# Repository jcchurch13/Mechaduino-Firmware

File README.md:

New release 11/26/2018!  The calibration table is now stored in flash memory!  (Many thanks to osresearch!) We've also fixed a couple of small bugs.
Here are some preliminary instructions on how to get your Mechaduino up and running.  For more details, see the Mechaduino Manual above!

## Bootloader:
You will need to make sure your Mechaduino has the latest Arduino Zero bootloader.  If you got your Mechaduino from Tropical Labs, it will already have this! Otherwise you will need an Atmel-ICE or similar SWD programmer...

## Firmware:

Compile the Mechaduino firmware in the Arduino IDE and upload to your Mechaduino.  (Mechaduino will appear as an Arduino Zero.)  

New firmware is in the default "master" branch. Older versions are available [here](https://github.com/jcchurch13/Mechaduino-Firmware/releases). 

## Calibration Routine:

The first thing you will need to do is run the encoder calibration routine.

With the Mechaduino connected to your computer, open a serial monitor (115200 baud) in the Arduino IDE.  You will need to provide V+ to the Mechaduino to power the motor drivers (needed to calibrate).  A menu should appear explaining the basic commands (you can call the menu up at any time by typing 'm').  Type "s" and press enter a couple times to verify that everything is working.  The Mechaduino should step like a stepper.  It is currently in open loop mode.  press "d" and the stepping direction will change.  

Now, make sure nothing will touch the Mechaduino’s shaft during the calibration routine. If possible, completely disconnect any load that is attached to the Mechaduino’s shaft.  Type "c" to start the calibration routine. The Mechaduino will now step through all full steps to calibrate the encoder. In the latest version of the firmware, the calibration table will automatically be stored in non-volatile flash memory. When this routine is complete, your Mechaduino is now calibrated!

## Basic Commands:

As long as you have "serialCheck();" in your main loop, you can use the following built in commands to control the mechaduino from a serial monitor:

s - step (steps one full step in open loop mode)

d - dir (changes step direction in open loop mode)

p - print angle [step count] , [assumed angle] , [encoder reading]

c - calibration routine

e - check encoder diagnostics

q - parameter query (prints current PID values and cal table)

x  -  position mode

v - velocity mode

t - torque mode

y - enable control loop (enter closed loop mode)

n - disable control loop (go back to open loop mode)

r - enter new setpoint (new setpoint for control loop)

j - step response

k - edit controller gains*

g - generate sine commutation table

m - print main menu

  ...see serialCheck() in Utils for more details

##License

All Mechaduino related materials are released under the
[Creative Commons Attribution Share-Alike 4.0 License](https://creativecommons.org/licenses/by-sa/4.0/)

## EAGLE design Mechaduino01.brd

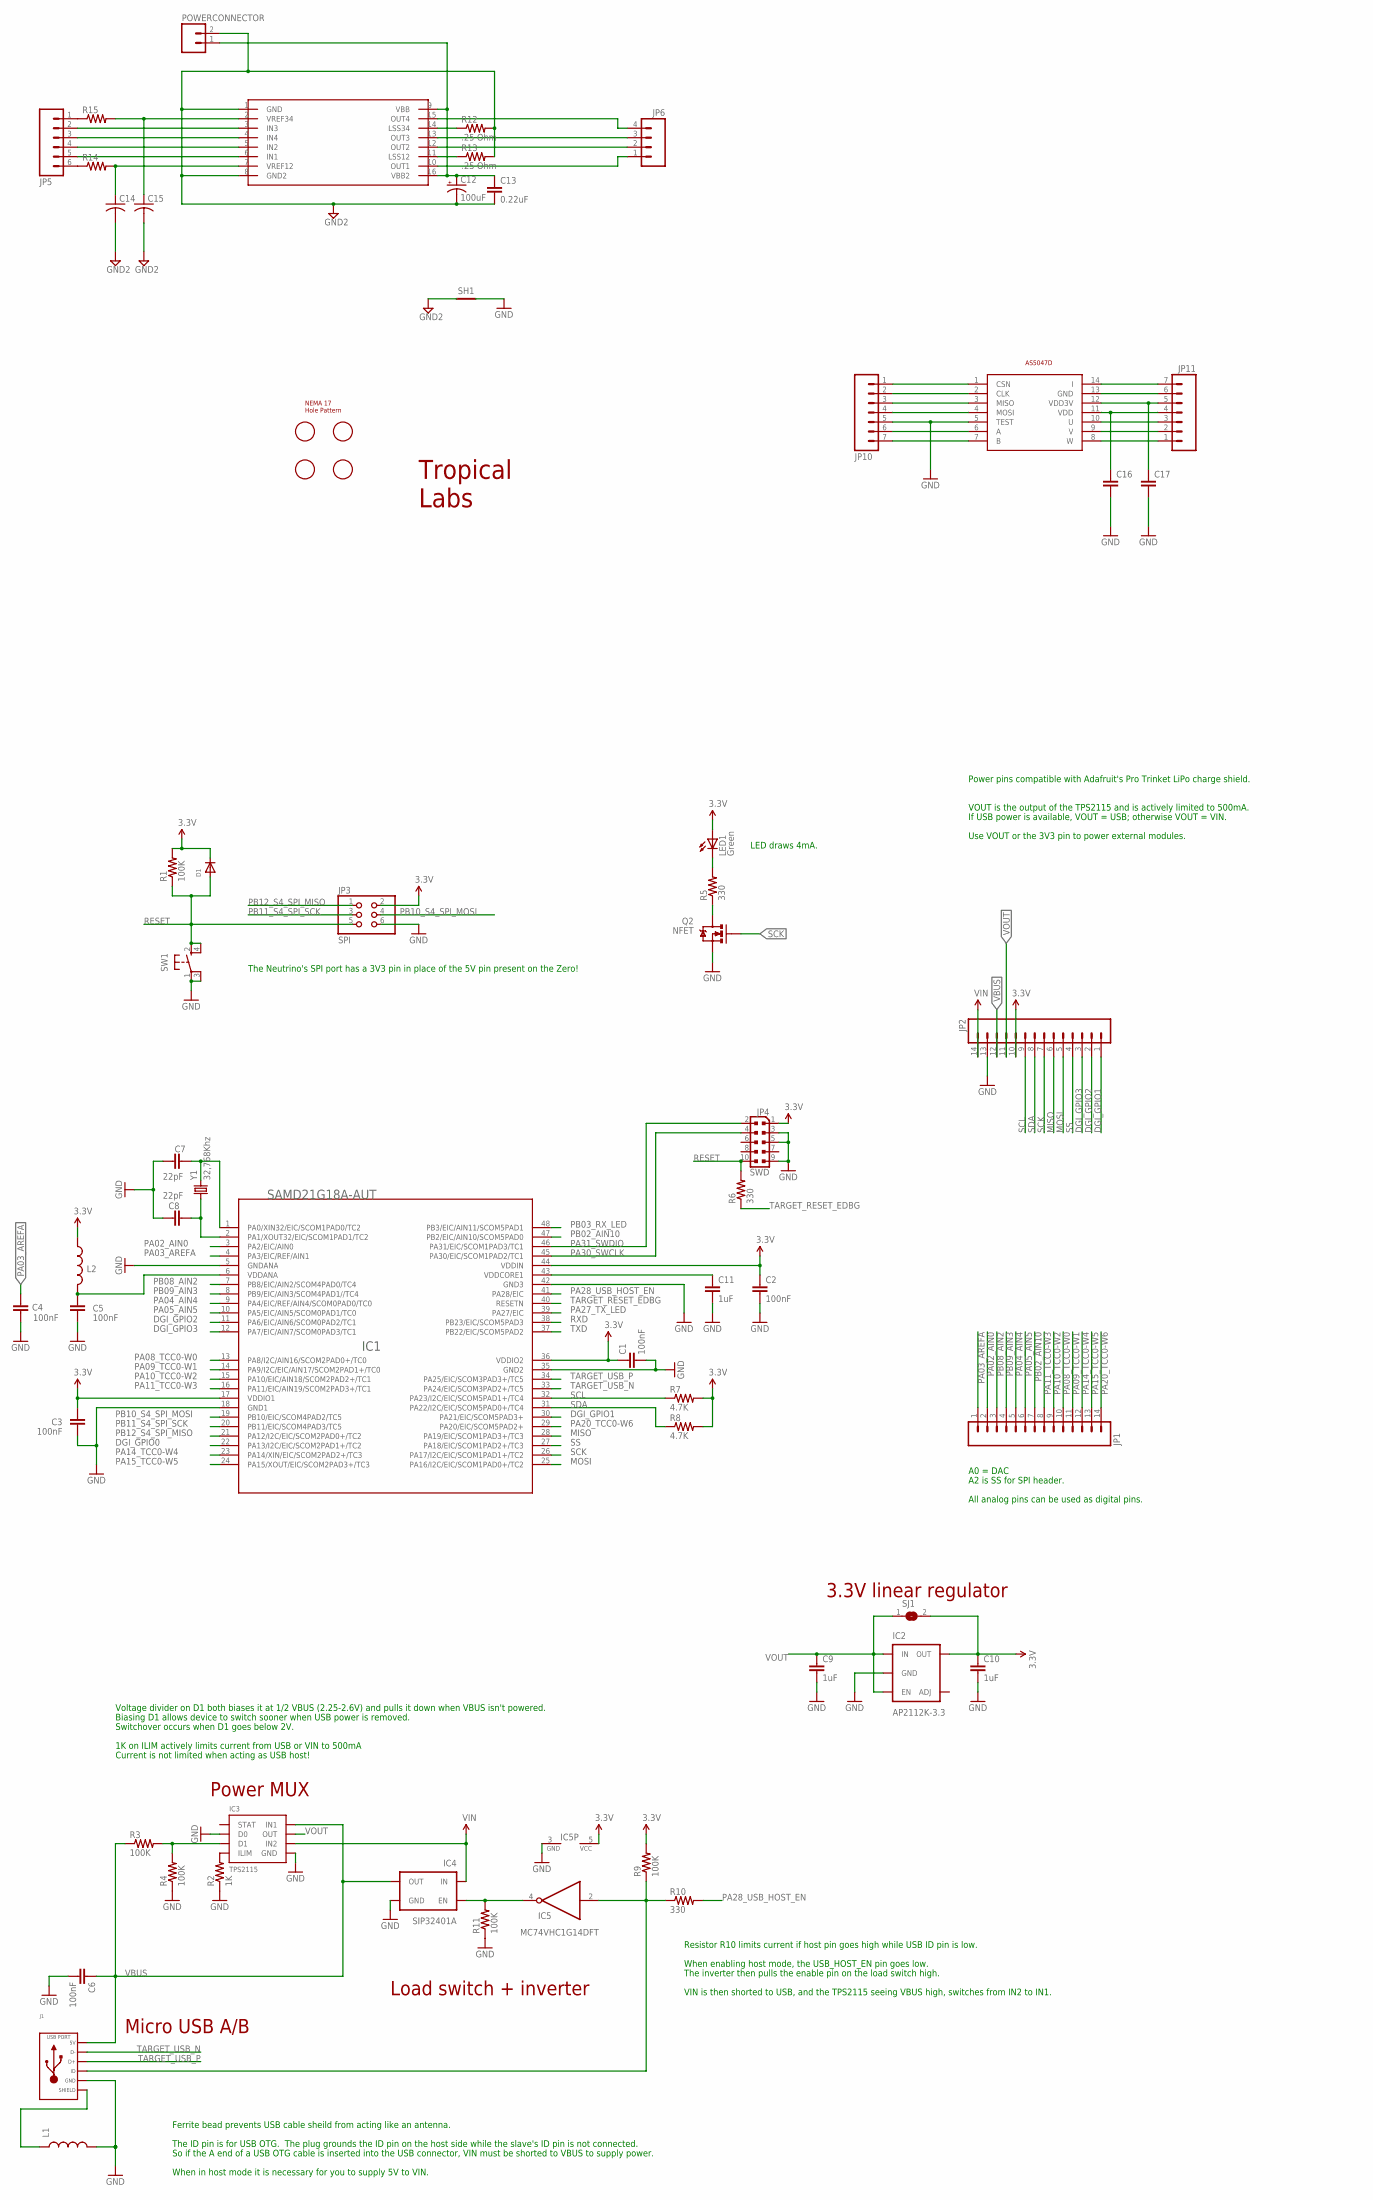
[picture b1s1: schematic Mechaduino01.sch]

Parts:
C1, C2, C3, C4, C5, C6: 100nF; 0402-CAP
C7, C8: 22pF; 0402-CAP
C9, C10, C11: 1uF; 0402-CAP
C12: 100uF; CPOL-RADIAL-100UF-25V
C13: 0.22uF; CAP-PTH-SMALLEZ
C14, C15: C-US050-035X075; C050-035X075
C16, C17: CAP0402; 0402-CAP
D1: DIODESOD-523; SOD-523
IC1: SAMD21G18A-AUT; INTEGRATEDCIRCUITS_TQFP48-7X7
IC2: AP2112K-3.3; SOT23-5
IC3: TPS2115; 8-VDFN
IC4: SIP32401A; TDFN4
IC5: MC74VHC1G14DFT; SC70-5
J1: USB_MICRO_RIGHT; MICROUSB-RIGHT
JP1, JP2: M14NOSILK_SMALLPADS; 1X14_NO_SILK_SMALLPADS
JP3: SPI; CONNETTORI_2X03
JP4: SWD; CONNETTORI_PINHEAD-2X5-P127
JP5: M06SILK_FEMALE_PTH; 1X06
JP6: M04PTH; 1X04
JP10, JP11: M07; 1X07
L1, L2: INDUCTOR0603-TDK; 0603-TDK
LED1: Green; CHIPLED_0805
POWERCONNECTOR: M025MM; SCREWTERMINAL-5MM-2
Q2: NFET; SOT323
R1, R3, R4, R9, R11: 100K; R0402-VISHAY
R2: 1K; R0402-VISHAY
R5, R6, R10: 330; R0402-VISHAY
R7, R8: 4.7K; R0402-VISHAY
R12, R13: .25 Ohm; 0204V
R14, R15: R-US_0204/2V; 0204V
SH1: SHORT-HA5; SHORT_ALL-50
SJ1: SJ
SW1: SPST_TACT-KMR2; KMR2
U$1: AVAGO_DRIVER; TSSOP16
U$2: NEMA17_HOLE_PATTERN
U$3: TROPICAL_LABS_LOGO_1LOGO2; LOGO2
U$4: AS5047D; TSSOP14
Y1: 32,768Khz; CRYSTAL-SMD-2.0X1.2

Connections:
3.3V: C1.1, C2.1, C3.2, C10.1, D1.K (C), IC1.17 (VDDIO1), IC1.36 (VDDIO2), IC1.44 (VDDIN), IC2.5 (OUT), IC5.5 (VCC), JP2.10, JP3.2, JP4.1, L2.1, LED1.A, R1.2, R7.2, R8.2, R9.2, SJ1.2
D1: IC3.3 (D1), R3.2, R4.2
DGI_GPIO0: IC1.22 (PA13/I2C/EIC/SCOM2PAD1+/TC2)
DGI_GPIO1: IC1.30 (PA21/EIC/SCOM5PAD3+), JP2.1
DGI_GPIO2: IC1.11 (PA6/EIC/AIN6/SCOM0PAD2/TC1), JP2.2
DGI_GPIO3: IC1.12 (PA7/EIC/AIN7/SCOM0PAD3/TC1), JP2.3
GND: C1.2, C2.2, C3.1, C4.2, C5.2, C6.2, C7.1, C8.1, C9.2, C10.2, C11.2, C16.2, C17.2, IC1.5 (GNDANA), IC1.18 (GND1), IC1.35 (GND2), IC1.42 (GND3), IC2.2 (GND), IC3.2 (D0), IC3.5 (GND), IC3.P0 (GND), IC3.V0 (GND), IC3.V1 (GND), IC3.V2 (GND), IC3.V3 (GND), IC3.V4 (GND), IC4.0 (GND), IC4.2 (GND), IC5.3 (GND), J1.5 (GND), JP2.13, JP3.6, JP4.3, JP4.5, JP4.9, JP10.5, L1.2, Q2.2 (S), R2.1, R4.1, R11.1, SH1.2, SW1.1, SW1.3 (P1), U$4.5 (TEST)
GND2: C12.2 (-), C13.2, C14.2, C15.2, POWERCONNECTOR.2, R12.2, R13.2, SH1.1, U$1.1 (GND), U$1.8 (GND2)
IC4_EN: IC4.4 (EN), IC5.4 (O), R11.2
ILIM: IC3.4 (ILIM), R2.2
MISO: IC1.28 (PA19/EIC/SCOM1PAD3+/TC3), JP2.6
MOSI: IC1.25 (PA16/I2C/EIC/SCOM1PAD0+/TC2), JP2.5
unnamed: LED1.C, R5.2
unnamed: R12.1, U$1.14 (LSS34)
unnamed: Q2.3 (D), R5.1
unnamed: R13.1, U$1.11 (LSS12)
unnamed: C12.1 (+), C13.1, POWERCONNECTOR.1, U$1.9 (VBB), U$1.16 (VBB2)
unnamed: C15.1, R15.2, U$1.2 (VREF34)
unnamed: IC5.2 (I), J1.4 (ID), R9.1, R10.1
unnamed: JP5.2, U$1.3 (IN3)
unnamed: JP5.3, U$1.4 (IN4)
unnamed: JP5.4, U$1.5 (IN2)
unnamed: JP5.5, U$1.6 (IN1)
unnamed: JP5.6, R14.1
unnamed: JP6.4, U$1.15 (OUT4)
unnamed: JP6.1, U$1.10 (OUT1)
unnamed: JP6.2, U$1.12 (OUT2)
unnamed: JP6.3, U$1.13 (OUT3)
unnamed: JP10.1, U$4.1 (CSN)
unnamed: JP10.2, U$4.2 (CLK)
unnamed: JP10.3, U$4.3 (MISO)
unnamed: JP10.4, U$4.4 (MOSI)
unnamed: JP5.1, R15.1
unnamed: JP10.6, U$4.6 (A)
unnamed: JP10.7, U$4.7 (B)
unnamed: JP11.1, U$4.8 (W)
unnamed: JP11.2, U$4.9 (V)
unnamed: JP11.3, U$4.10 (U)
unnamed: C16.1, JP11.4, U$4.11 (VDD)
unnamed: C17.1, JP11.5, U$4.12 (VDD3V)
unnamed: JP11.6, U$4.13 (GND)
unnamed: JP11.7, U$4.14 (I)
unnamed: C14.1, R14.2, U$1.7 (VREF12)
PA00_XIN32: C7.2, IC1.1 (PA0/XIN32/EIC/SCOM1PAD0/TC2), Y1.2
PA01_XOUT32: C8.2, IC1.2 (PA1/XOUT32/EIC/SCOM1PAD1/TC2), Y1.1
PA02_AIN0: IC1.3 (PA2/EIC/AIN0), JP1.2
PA03_AREFA: C4.1, IC1.4 (PA3/EIC/REF/AIN1), JP1.1
PA04_AIN4: IC1.9 (PA4/EIC/REF/AIN4/SCOM0PAD0/TC0), JP1.5
PA05_AIN5: IC1.10 (PA5/EIC/AIN5/SCOM0PAD1/TC0), JP1.6
PA08_TCC0-W0: IC1.13 (PA8/I2C/AIN16/SCOM2PAD0+/TC0), JP1.10
PA09_TCC0-W1: IC1.14 (PA9/I2C/EIC/AIN17/SCOM2PAD1+/TC0), JP1.11
PA10_TCC0-W2: IC1.15 (PA10/EIC/AIN18/SCOM2PAD2+/TC1), JP1.9
PA11_TCC0-W3: IC1.16 (PA11/EIC/AIN19/SCOM2PAD3+/TC1), JP1.8
PA14_TCC0-W4: IC1.23 (PA14/XIN/EIC/SCOM2PAD2+/TC3), JP1.12
PA15_TCC0-W5: IC1.24 (PA15/XOUT/EIC/SCOM2PAD3+/TC3), JP1.13
PA20_TCC0-W6: IC1.29 (PA20/EIC/SCOM5PAD2+), JP1.14
PA27_TX_LED: IC1.39 (PA27/EIC)
PA28_USB_HOST_EN: IC1.41 (PA28/EIC), R10.2
PA30_SWCLK: IC1.45 (PA30/EIC/SCOM1PAD2/TC1), JP4.4
PA31_SWDIO: IC1.46 (PA31/EIC/SCOM1PAD3/TC1), JP4.2
PB02_AIN10: IC1.47 (PB2/EIC/AIN10/SCOM5PAD0), JP1.7
PB03_RX_LED: IC1.48 (PB3/EIC/AIN11/SCOM5PAD1)
PB08_AIN2: IC1.7 (PB8/EIC/AIN2/SCOM4PAD0/TC4), JP1.3
PB09_AIN3: IC1.8 (PB9/EIC/AIN3/SCOM4PAD1//TC4), JP1.4
PB10_S4_SPI_MOSI: IC1.19 (PB10/EIC/SCOM4PAD2/TC5), JP3.4
PB11_S4_SPI_SCK: IC1.20 (PB11/EIC/SCOM4PAD3/TC5), JP3.3
PB12_S4_SPI_MISO: IC1.21 (PA12/I2C/EIC/SCOM2PAD0+/TC2), JP3.1
RESET: D1.A, JP3.5, JP4.10, R1.1, R6.2, SW1.2 (S), SW1.4 (S1)
RXD: IC1.38 (PB23/EIC/SCOM5PAD3)
SCK: IC1.26 (PA17/I2C/EIC/SCOM1PAD1+/TC2), JP2.7, Q2.1 (G)
SCL: IC1.32 (PA23/I2C/EIC/SCOM5PAD1+/TC4), JP2.9, R7.1
SDA: IC1.31 (PA22/I2C/EIC/SCOM5PAD0+/TC4), JP2.8, R8.1
SHIELD: J1.S1 (SLD), J1.S2 (SLD), J1.S3 (SLD), J1.S4 (SLD), J1.S5 (SLD), J1.S6 (SLD), J1.S7 (SLD), J1.S8 (SLD), L1.1
SS: IC1.27 (PA18/EIC/SCOM1PAD2+/TC3), JP2.4
TARGET_RESET_EDBG: IC1.40 (RESETN), R6.1
TARGET_USB_N: IC1.33 (PA24/EIC/SCOM3PAD2+/TC5), J1.2 (D-)
TARGET_USB_P: IC1.34 (PA25/EIC/SCOM3PAD3+/TC5), J1.3 (D+)
TXD: IC1.37 (PB22/EIC/SCOM5PAD2)
VBUS: C6.1, IC3.8 (IN1), IC4.1 (OUT), J1.1 (5V), JP2.12, R3.1
VDDANA: C5.1, IC1.6 (VDDANA), L2.2
VDDCORE: C11.1, IC1.43 (VDDCORE1)
VIN: IC3.6 (IN2), IC4.3 (IN), JP2.14
VOUT: C9.1, IC2.1 (IN), IC2.3 (EN), IC3.7 (OUT), JP2.11, SJ1.1

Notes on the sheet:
A0 = DAC
All analog pins can be used as digital pins.
Power pins compatible with Adafruit's Pro Trinket LiPo charge shield.
LED draws 4mA.
The Neutrino's SPI port has a 3V3 pin in place of the 5V pin present on the Zero!
A2 is SS for SPI header.
VOUT is the output of the TPS2115 and is actively limited to 500mA.
If USB power is available, VOUT = USB; otherwise VOUT = VIN.
Use VOUT or the 3V3 pin to power external modules.
Micro USB A/B
Ferrite bead prevents USB cable sheild from acting like an antenna.
The ID pin is for USB OTG. The plug grounds the ID pin on the host side while the slave's ID pin is not connected.
So if the A end of a USB OTG cable is inserted into the USB connector, VIN must be shorted to VBUS to supply power.
3.3V linear regulator
When in host mode it is necessary for you to supply 5V to VIN.
1K on ILIM actively limits current from USB or VIN to 500mA
Voltage divider on D1 both biases it at 1/2 VBUS (2.25-2.6V) and pulls it down when VBUS isn't powered.
Current is not limited when acting as USB host!
Biasing D1 allows device to switch sooner when USB power is removed.
Switchover occurs when D1 goes below 2V.
When enabling host mode, the USB_HOST_EN pin goes low.
Resistor R10 limits current if host pin goes high while USB ID pin is low.
Load switch + inverter
The inverter then pulls the enable pin on the load switch high.
Power MUX
VIN is then shorted to USB, and the TPS2115 seeing VBUS high, switches from IN2 to IN1.

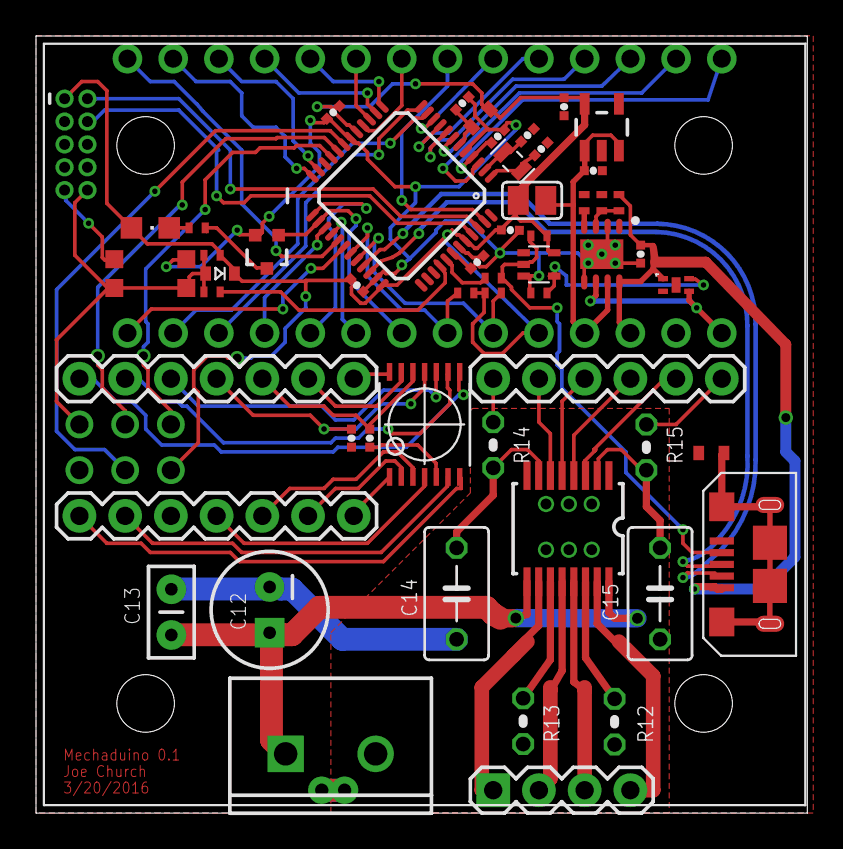
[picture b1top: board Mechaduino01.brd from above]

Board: 2 copper layers, 42.8 x 43.2 mm, 60 parts (1 on the bottom side), 78 nets.

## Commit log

2016-01-03 :boom::camel: Added .gitattributes & .gitignore files
2016-01-03 copied from Stepper_Servo_Prototype_1
2016-01-08 implemented wrap function
    works great
2016-01-26 better command_w
    now command_w finds i_step 0 and correct dir based on positive encoder
    direction
    need to get read of i_step/serostate modifiers in c/z?
    output angles seem to to work off the bat
    may need to get rid of 'c' or 'z' functions
2016-01-29 implemented TC5 interrupt, PID
    TC5 interrupt running at 2.5kHz
    great pid settings, but pid is suspect... pure kp behaves odd
2016-01-30 added arduino pid library style pid
    works ok, but oscillates around 0
2016-01-30 Fixed wrap with yw (ywrapped)
    no zero oscillation with arduino style pid
2016-01-30 velocity mode works...
2016-02-08 fixed commandW
    working great on v00-1
    starting v00-2 (NEMA 23)
2016-03-17 updates to "clean" version
2016-03-17 Revert "updates to "clean" version"
    This reverts commit 90bb68a3498d13031456764343cb697794e51088.
2016-03-17 Revert "Revert "updates to "clean" version""
    This reverts commit fd57af2a47592322c2b997973fcab205f28407ed.
2016-03-17 added current parameter command
    hit 'q' for paramaeters, also added v mode and cleaned up
2016-03-17 adjusting velocity mode
2016-03-24 copied from Mechaduino 0.0
    baseline
2016-03-24 Revert "copied from Mechaduino 0.0"
    This reverts commit c7bb6a98085dd24362716008a52ce136a40975a1.
2016-03-30 dispenser pid constants
2016-03-31 electronic gearing/haptics
    implemented with analog setpoints and two motors:
    M1 position --> M2 setpoint
    M2 position --> M1 setpoint
    It works! Could use some filtering to remove noise, but not bad for
    first attempt!
2016-04-01 i2c interrupt works
    also verified (with example code) that Mechaduino_00 hardware works as
    i2c and master using Wire lib. examples
2016-05-19 added Mechaduino 01
    pretty much the same except A2 is CS for encoder instead of A5
2016-05-19 deleted old setpoint functions
    and other outdated stuff
2016-06-02 Created license file
2016-06-06 Moving functions to separate file
2016-06-19 moving to multiple files
2016-06-19 moving to seperate files
2016-06-19 Multi File test
2016-06-19 Revert "moving to seperate files"
    This reverts commit ec257edda9c296e06ba1765797bdf8fc7b968cc0.
2016-06-19 Revert "Moving functions to separate file"
    This reverts commit 0127fb6913699b31a3e6c36ecd3e67030672f844.
2016-06-26 changed uMAX
2016-06-26 adjusted gains
2016-06-26 recal
2016-06-26 multimode demo
2016-06-26 edited demo
2016-07-08 hmmm...
2016-07-08 Revert "hmmm..."
    This reverts commit 6299245438a9cfd7f93071a908f60e6bef0253a6.
2016-07-08 Revert "multimode demo"
    This reverts commit 3e72f6857e3aaa392333ee65dc70ab10476183ec.
2016-07-08 fixed some stuff
2016-07-08 add new files
2016-07-08 Added proper ifdefs
2016-07-08 moving things around, defaulting to include all possible libraries at first for compilation ease. Will remove extraneous later
2016-07-08 mechaduino_function stuff to new locations and deleted
2016-07-09 moving stuff, bumping from error to error
2016-07-09 moving functions to util as they spout errors
2016-07-09 parameteredit fncs to utils
2016-07-09 not sure where these constants go, they're going to state for now
2016-07-09 moved sine lookup and mod stuff
2016-07-09 moved TCInterrupt stuff
2016-07-09 moved last few fncs to utils
2016-07-09 got Ts and such working. learned about multiple declarations
2016-07-09 think i got this multiple definition thing licked. moved pin vars
2016-07-09 moved rest of parameter vars except for lookups, which haven't thrown errors yet
2016-07-09 moved state vars
2016-07-09 moved last state vars. joint COMPILES
2016-07-09 clean up, removed unnecessary includes
2016-07-09 moved lookup table to parameters.cpp
    also removed commented code in loop
2016-07-09 cleaned up main file some more
2016-07-19 added includes to main
2016-07-22 added readme
2016-07-22 fixing image
2016-07-22 added firmware structure
2016-07-22 fixed license formatting
2016-07-22 cleaned up a little bit
2016-08-07 Improved menus
2016-08-08 Added better current limiting
2016-09-27 some minor fixes
    pi to more digits, corrected fs dependence in velocity loop
2016-09-27 Fixed minor cal routine bug
2016-10-04 Added some more comments
2016-10-05 fixed iMAX
2016-10-15 Added analogFastWrite command
    The latest arduino zero board files (1.6.7 and up) have a much lower PWM
    frequency than previous versions (732.4Hz , down from 187.5kHz). This
    causes audible hissing when used with the Mechaduino. We added the
    analogFastWrite command to provide 187.5kHz PWM to eliminate this issue.
2016-10-20 Fixed capitalization error
    state.h -> State.h
2016-10-31 Added Hybrid Step Mode
2016-10-31 cleaned up loop
2016-10-31 cleaned up after merge
2016-10-31 editing hybridStep
2016-11-05 developing hybrid step mode
2016-11-08 SerialCheck must be uncommented in loop
2016-11-08 updated readme with links
2016-11-11 removed old files
2016-11-12 added files
2016-11-15 began cleaning up controller
2016-11-15 Added lots of comments to utils
2016-11-16 Fixed menus
2016-11-16 more clean up
    mostly in controller.cpp
2016-11-18 faster SPI, Digital Write
2016-11-18 changed analogFastWrite resolution to 10 bit
    also fixed spi stuff
2016-11-23 changed PWM to true 10-bit, also fixed aps in onestep
2016-11-23 removed macros file
2016-11-23 Return to 8 bit pwm...
    10 bit worked, lowers pwm frequency... seemed to be more audible noise
    and not as smooth... may revisit at some point.
2016-11-23 developong sineGen
2016-11-23 now supports 0.9 degree steppers
2016-11-23 ...more 0.9 support fixes
2016-11-23 Better/faster output function
    made Fs adjustable.. now set to 6kHz
2016-11-24 developing step response
2016-11-24 changed cal letter to 'c', cleaned up
2016-11-25 changed to one sineGen table..
    Was running out of SRAM in 400 step cal routine... now 400 step works.
2016-11-25 more clean up
2016-11-25 cleaned up, added documentation
2016-11-25 clean up, fixed parameter query
    ...moved declarations between state and parameter files (makes more
    sense now).
2016-11-25 clean up after big merge
2016-11-25 step response looks pretty good
2016-11-27 more improvements
2016-11-27 Revert "first commit"
    This reverts commit 0f91d381ae8e9491c20469da15cd81e01dfe70ee.
2016-11-29 Revert "more improvements"
    This reverts commit 2a2d0a18485f85471a3c1eef626906117915eafb.
2016-11-29 Revert "Revert "more improvements""
    This reverts commit 75b1159b6c60dd774297a2c193a2c027d893a0ea.
2016-11-29 temporary fix for memory bug
2016-11-29 temporary fix for memory bug
    sineGen seems to overwrite stepNumber... better fix coming soon
2016-11-29 fixed memory issue
    sine table no longer stored in ram. It can now be generated from menu.
2016-12-03 changing pin definitions to defines from constants
2016-12-07 fixed fast digital write stuff
    using defines now for readability
2016-12-07 note on sinegen
2016-12-09 fixed a few things
2016-12-10 more clean up, added configStepDir()
2016-12-11 adding enable..
2016-12-12 lots of clean up
    enable now works
2016-12-12 changed spr default back to 200
2016-12-14 moved control algorithms back to control.cpp
2016-12-20 added LPFs to control loops
2016-12-22 fixed velocity loop gains
2016-12-28 developing moveRel command
2016-12-28 moveAbs and moveRel work, moved to utils
2016-12-29 minor edits
2016-12-29 added manual
2016-12-29 fixed readme
2016-12-29 removed old photo
2016-12-29 cleared lookup table
2017-01-05 fixed velocity mode lpf editing
2017-01-05 removed lookup before merge
2017-01-05 fixed parameter edit bug
2017-05-04 removed 01 from name
2017-05-04 changed version, fixed menu 't' issue
2017-05-04 actually fixed 't' in menu...
2017-05-04 changed to single phase cal
2017-05-06 Updated manual
2017-05-06 Removed lookup table
2017-05-06 replaced hearer image
2017-05-06 replaced old photo
2017-05-06 fixed typo
2017-05-31 Fixed cal bug
2017-06-04 fixed stepangle typo
2018-06-09 Store calibration lookup table in the flash using the FlashStorage library
2018-06-09 cleanup sine table
2018-06-09 Hold current position when closed loop is engaged.
    This also correctly computes the current angle using the lookup
    table, rather than having an approximation of the encoder value.
2018-11-24 Minor edits
    Fixed (mostly) an issue with holding the current position when entering
    closed loop mode. This works unless the shaft has moved through 0
    degrees.
    Also added a "calibration complete" message
2018-11-26 Set phase currents to zero when disabled.
2018-11-26 Added new Manual!
2018-11-26 fixed version number

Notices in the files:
parts and their libraries:
SparkFun-Connectors: Licensing: Creative Commons ShareAlike 4.0 International - https://creativecommons.org/licenses/by-sa/4.0
